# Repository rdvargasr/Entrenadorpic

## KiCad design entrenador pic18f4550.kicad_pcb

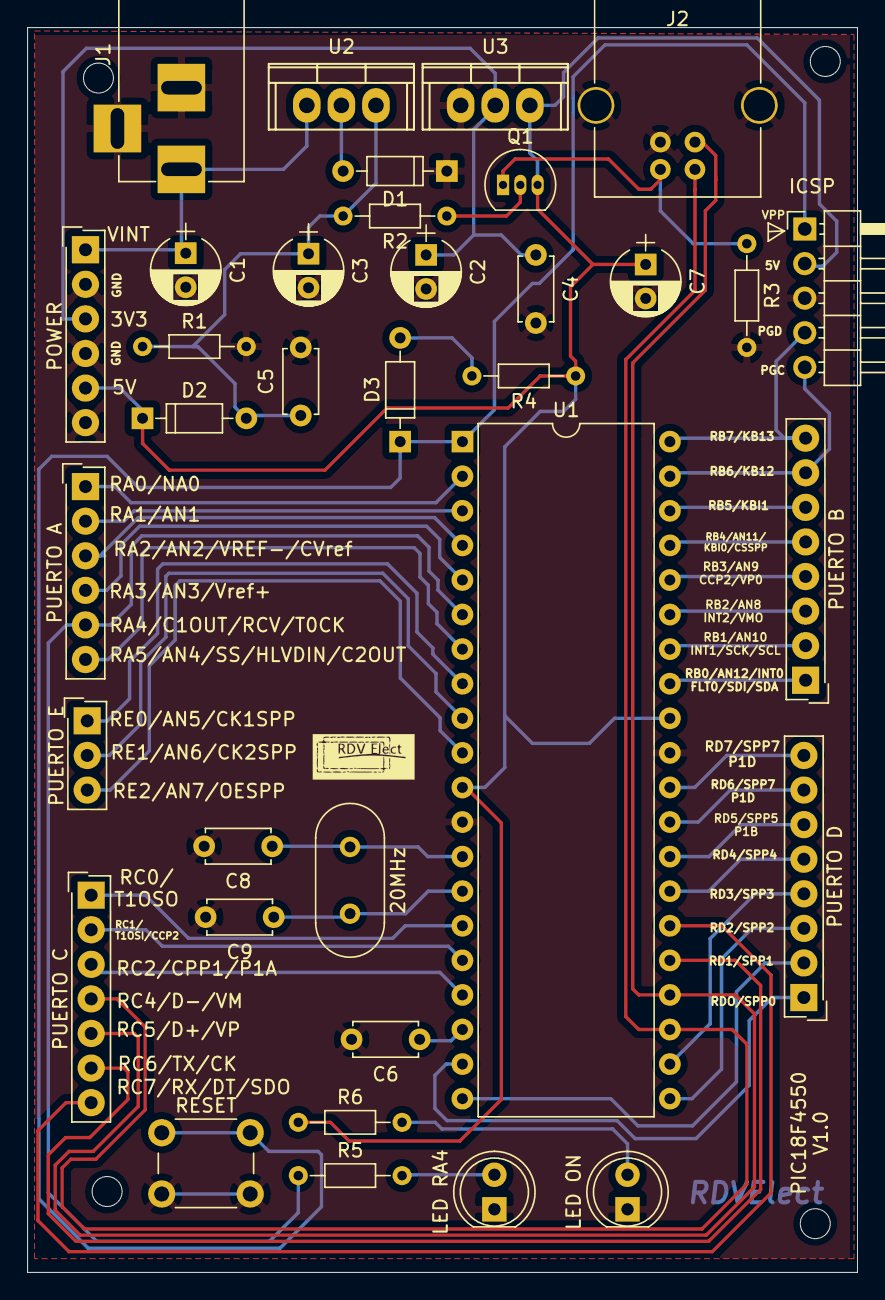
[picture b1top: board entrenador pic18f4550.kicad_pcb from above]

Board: 2 copper layers, 61.0 x 91.4 mm, 34 parts (0 on the bottom side), 47 nets.

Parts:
20MHz: 20MHZ; Crystal_HC18-U_Vertical
C1: 47uF; CP_Radial_D5.0mm_P2.50mm
C2, C3, C7: 100uF; CP_Radial_D5.0mm_P2.50mm
C4, C5: 100nF; C_Disc_D4.7mm_W2.5mm_P5.00mm
C6: 47uF; C_Disc_D4.7mm_W2.5mm_P5.00mm
C8, C9: 15pF; C_Disc_D4.7mm_W2.5mm_P5.00mm
D1, D2, D3: 1N4148; D_DO-35_SOD27_P7.62mm_Horizontal
J1: Barrel_Jack_Switch; BARREL_JACK
J2: USB_B
LED ON: LED; LED_D5.0mm
LED RA4: LED; LED_D5.0mm
POWER: POWER; SL-106-X-XX_1x06
PUERTO A: PUERTO A; SL-106-X-XX_1x06
PUERTO B: PUERTO B; SL-108-X-XX_1x08
PUERTO C: PUERTO C; SL-107-X-XX_1x07
PUERTO D: PUERTOD; SL-108-X-XX_1x08
PUERTO E: PUERTO E; SL-103-X-XX_1x03
Q1: 2N3906; TO-92_Inline_Narrow_Oval
R1, R2: 5.6K; R_Axial_DIN0204_L3.6mm_D1.6mm_P7.62mm_Horizontal
R3, R4: 10K; R_Axial_DIN0204_L3.6mm_D1.6mm_P7.62mm_Horizontal
R5, R6: 330; R_Axial_DIN0204_L3.6mm_D1.6mm_P7.62mm_Horizontal
RESET: SW_Push; SW_PUSH_6mm
U1: PIC18F4450-IP; DIP-40_W15.24mm
U2: L7805; TO-220
U3: LM1117-3.3; TO-220

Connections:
/3V3: C2.1, C4.1, POWER.3, U3.2
/MCLR: D3.1, RESET.1, U1.1
/OSC1: 20MHz.1, C8.1, U1.13
/OSC2: 20MHz.2, C9.1, U1.14
/RA0: PUERTO A.1, U1.2
/RA1: PUERTO A.2, U1.3
/RA2: PUERTO A.3, U1.4
/RA3: PUERTO A.4, U1.5
/RA4: PUERTO A.5, R5.1, U1.6
/RA5: PUERTO A.6, U1.7
/RB0: PUERTO B.1, U1.33
/RB1: PUERTO B.2, U1.34
/RB2: PUERTO B.3, U1.35
/RB3: PUERTO B.4, U1.36
/RB4: PUERTO B.5, U1.37
/RB5: PUERTO B.6, U1.38
/RB6: PUERTO B.7, U1.39
/RB7: PUERTO B.8, U1.40
/RC0: PUERTO C.1, U1.15
/RC1: PUERTO C.2, U1.16
/RC2: PUERTO C.3, U1.17
/RC4: J2.2, PUERTO C.4, U1.23
/RC5: J2.3, PUERTO C.5, U1.24
/RC6: PUERTO C.6, U1.25
/RC7: PUERTO C.7, U1.26
/RD0: PUERTO D.1, U1.19
/RD1: PUERTO D.2, U1.20
/RD2: PUERTO D.3, U1.21
/RD3: PUERTO D.4, U1.22
/RD4: PUERTO D.5, U1.27
/RD5: PUERTO D.6, U1.28
/RD6: PUERTO D.7, U1.29
/RD7: PUERTO D.8, U1.30
/RE0: PUERTO E.1, U1.8
/RE1: PUERTO E.2, U1.9
/RE2: PUERTO E.3, U1.10
/VBUS: J2.1, Q1.1, R3.1
GND: C1.2, C2.2, C3.2, C4.2, C5.2, C6.2, C7.2, C8.2, C9.2, D1.1, J1.2, J1.3, J2.4, J2.5, LED ON.1, LED RA4.1, POWER.2, POWER.4, POWER.6, R1.2, R3.2, RESET.2, U1.12, U1.31, U3.1
unnamed: C3.1, C5.1, D2.2, R1.1, R2.2, U2.3
unnamed: C6.1, U1.18
unnamed: D1.2, U2.2
unnamed: D3.2, R4.2
unnamed: LED RA4.2, R5.2
unnamed: LED ON.2, R6.2
unnamed: Q1.2, R2.1
VD: C1.1, J1.1, POWER.1, U2.1
VDD: C7.1, D2.1, POWER.5, Q1.3, R4.1, R6.1, U1.11, U1.32, U3.3

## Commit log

2022-05-07 version1
